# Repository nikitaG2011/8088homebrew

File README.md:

just run the make comand to assemble the code

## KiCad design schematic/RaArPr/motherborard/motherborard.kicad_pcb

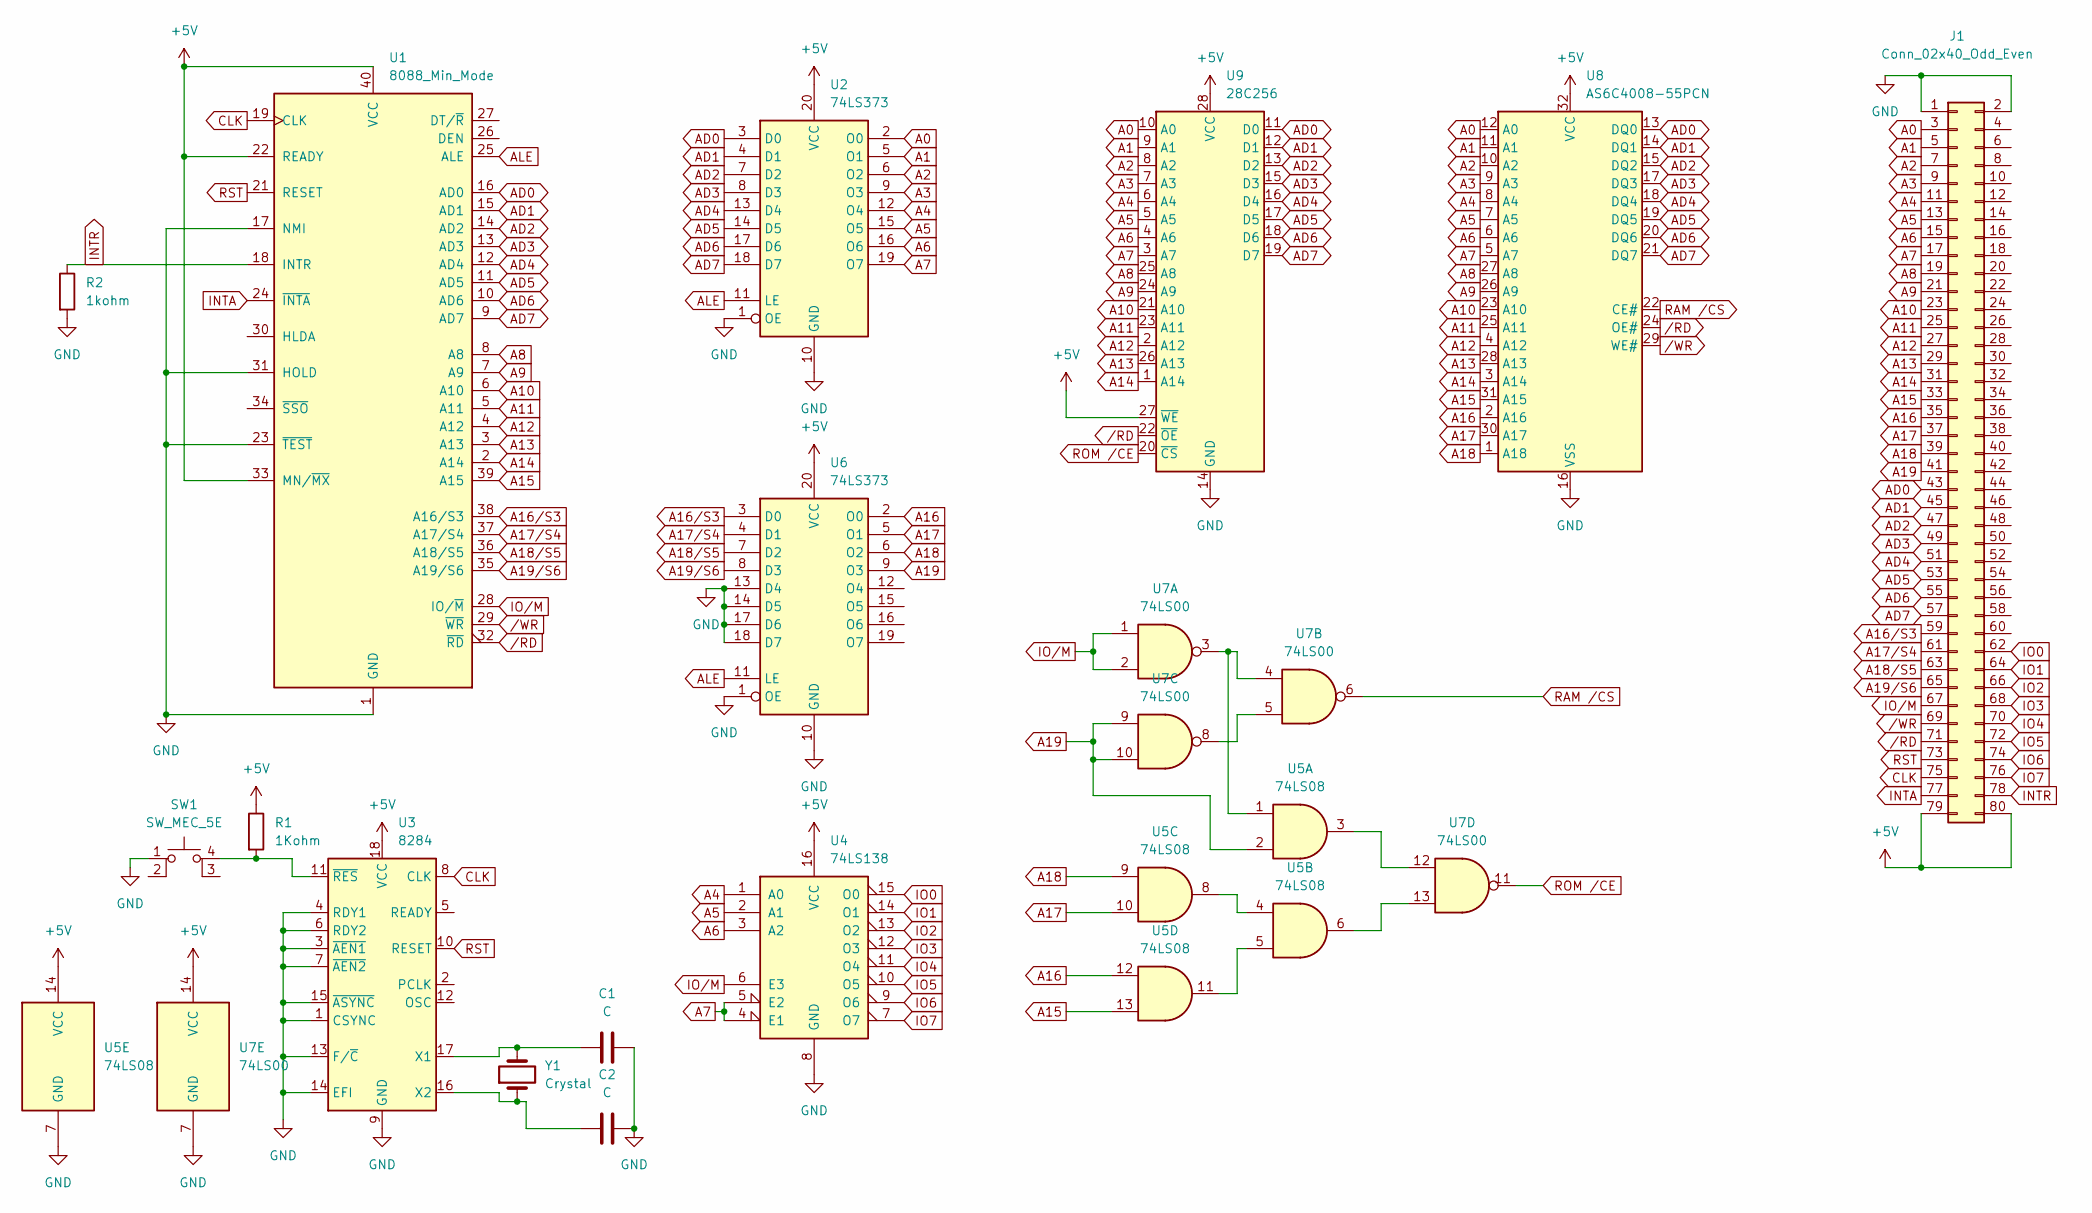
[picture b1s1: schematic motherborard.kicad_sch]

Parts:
C1, C2: C; C_Axial_L3.8mm_D2.6mm_P7.50mm_Horizontal
J1: Conn_02x40_Odd_Even; PinHeader_2x40_P2.54mm_Horizontal
R1: 1Kohm; R_Axial_DIN0204_L3.6mm_D1.6mm_P5.08mm_Horizontal
R2: 1kohm; R_Axial_DIN0204_L3.6mm_D1.6mm_P5.08mm_Horizontal
SW1: SW_MEC_5E; SW_MEC_5GSH9
U1: 8088_Min_Mode; DIP-40_W15.24mm
U2, U6: 74LS373; DIP-20_W7.62mm_Socket_LongPads
U3: 8284; DIP-18_W7.62mm_Socket_LongPads
U4: 74LS138; DIP-16_W7.62mm_Socket_LongPads
U5: 74LS08; DIP-14_W7.62mm_Socket_LongPads
U7: 74LS00; DIP-14_W7.62mm_Socket_LongPads
U8: AS6C4008-55PCN; DIP-32_W15.24mm_Socket_LongPads
U9: 28C256; DIP-28_W15.24mm_LongPads
Y1: Crystal; Crystal_HC18-U_Horizontal

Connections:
+5V: J1.79, J1.80, R1.1, U1.22 (READY), U1.33 (MN/~MX), U1.40 (VCC), U2.20 (VCC), U3.18 (VCC), U4.16 (VCC), U5.14 (VCC), U6.20 (VCC), U7.14 (VCC), U8.32 (VCC), U9.27 (~WE), U9.28 (VCC)
A0: J1.3, U2.2 (O0), U8.12 (A0), U9.10 (A0)
A1: J1.5, U2.5 (O1), U8.11 (A1), U9.9 (A1)
A2: J1.7, U2.6 (O2), U8.10 (A2), U9.8 (A2)
A3: J1.9, U2.9 (O3), U8.9 (A3), U9.7 (A3)
A4: J1.11, U2.12 (O4), U4.1 (A0), U8.8 (A4), U9.6 (A4)
A5: J1.13, U2.15 (O5), U4.2 (A1), U8.7 (A5), U9.5 (A5)
A6: J1.15, U2.16 (O6), U4.3 (A2), U8.6 (A6), U9.4 (A6)
A7: J1.17, U2.19 (O7), U4.4 (E1), U4.5 (E2), U8.5 (A7), U9.3 (A7)
A8: J1.19, U1.8 (A8), U8.27 (A8), U9.25 (A8)
A9: J1.21, U1.7 (A9), U8.26 (A9), U9.24 (A9)
A10: J1.23, U1.6 (A10), U8.23 (A10), U9.21 (A10)
A11: J1.25, U1.5 (A11), U8.25 (A11), U9.23 (A11)
A12: J1.27, U1.4 (A12), U8.4 (A12), U9.2 (A12)
A13: J1.29, U1.3 (A13), U8.28 (A13), U9.26 (A13)
A14: J1.31, U1.2 (A14), U8.3 (A14), U9.1 (A14)
A15: J1.33, U1.39 (A15), U5.13, U8.31 (A15)
A16: J1.35, U5.12, U6.2 (O0), U8.2 (A16)
A16/S3: J1.59, U1.38 (A16/S3), U6.3 (D0)
A17: J1.37, U5.10, U6.5 (O1), U8.30 (A17)
A17/S4: J1.61, U1.37 (A17/S4), U6.4 (D1)
A18: J1.39, U5.9, U6.6 (O2), U8.1 (A18)
A18/S5: J1.63, U1.36 (A18/S5), U6.7 (D2)
A19: J1.41, U5.2, U6.9 (O3), U7.9, U7.10
A19/S6: J1.65, U1.35 (A19/S6), U6.8 (D3)
AD0: J1.43, U1.16 (AD0), U2.3 (D0), U8.13 (DQ0), U9.11 (D0)
AD1: J1.45, U1.15 (AD1), U2.4 (D1), U8.14 (DQ1), U9.12 (D1)
AD2: J1.47, U1.14 (AD2), U2.7 (D2), U8.15 (DQ2), U9.13 (D2)
AD3: J1.49, U1.13 (AD3), U2.8 (D3), U8.17 (DQ3), U9.15 (D3)
AD4: J1.51, U1.12 (AD4), U2.13 (D4), U8.18 (DQ4), U9.16 (D4)
AD5: J1.53, U1.11 (AD5), U2.14 (D5), U8.19 (DQ5), U9.17 (D5)
AD6: J1.55, U1.10 (AD6), U2.17 (D6), U8.20 (DQ6), U9.18 (D6)
AD7: J1.57, U1.9 (AD7), U2.18 (D7), U8.21 (DQ7), U9.19 (D7)
ALE: U1.25 (ALE), U2.11 (LE), U6.11 (LE)
CLK: J1.75, U1.19 (CLK), U3.8 (CLK)
GND: C1.2, C2.2, J1.1, J1.2, R2.2, SW1.1, U1.1 (GND), U1.17 (NMI), U1.20 (GND), U1.23 (~TEST), U1.31 (HOLD), U2.1 (OE), U2.10 (GND), U3.1 (CSYNC), U3.3 (~AEN1), U3.4 (RDY1), U3.6 (RDY2), U3.7 (~AEN2), U3.9 (GND), U3.13 (F/~C), U3.14 (EFI), U3.15 (~ASYNC), U4.8 (GND), U5.7 (GND), U6.1 (OE), U6.10 (GND), U6.13 (D4), U6.14 (D5), U6.17 (D6), U6.18 (D7), U7.7 (GND), U8.16 (VSS), U9.14 (GND)
INTA: J1.77, U1.24 (~INTA)
INTR: J1.78, R2.1, U1.18 (INTR)
IO0: J1.62, U4.15 (O0)
IO1: J1.64, U4.14 (O1)
IO2: J1.66, U4.13 (O2)
IO3: J1.68, U4.12 (O3)
IO4: J1.70, U4.11 (O4)
IO5: J1.72, U4.10 (O5)
IO6: J1.74, U4.9 (O6)
IO7: J1.76, U4.7 (O7)
IO/M: J1.67, U1.28 (IO/~M), U4.6 (E3), U7.1, U7.2
unnamed: R1.2, SW1.4 (A), U3.11 (~RES)
unnamed: C1.1, U3.17 (X1), Y1.2
unnamed: C2.1, U3.16 (X2), Y1.1
unnamed: U5.1, U7.3, U7.4
unnamed: U5.3, U7.12
unnamed: U5.4, U5.8
unnamed: U5.6, U7.13
unnamed: U5.5, U5.11
unnamed: U7.5, U7.8
RAM /CS: U7.6, U8.22 (CE#)
ROM /CE: U7.11, U9.20 (~CS)
RST: J1.73, U1.21 (RESET), U3.10 (RESET)
/RD: J1.71, U1.32 (~RD), U8.24 (OE#), U9.22 (~OE)
/WR: J1.69, U1.29 (~WR), U8.29 (WE#)

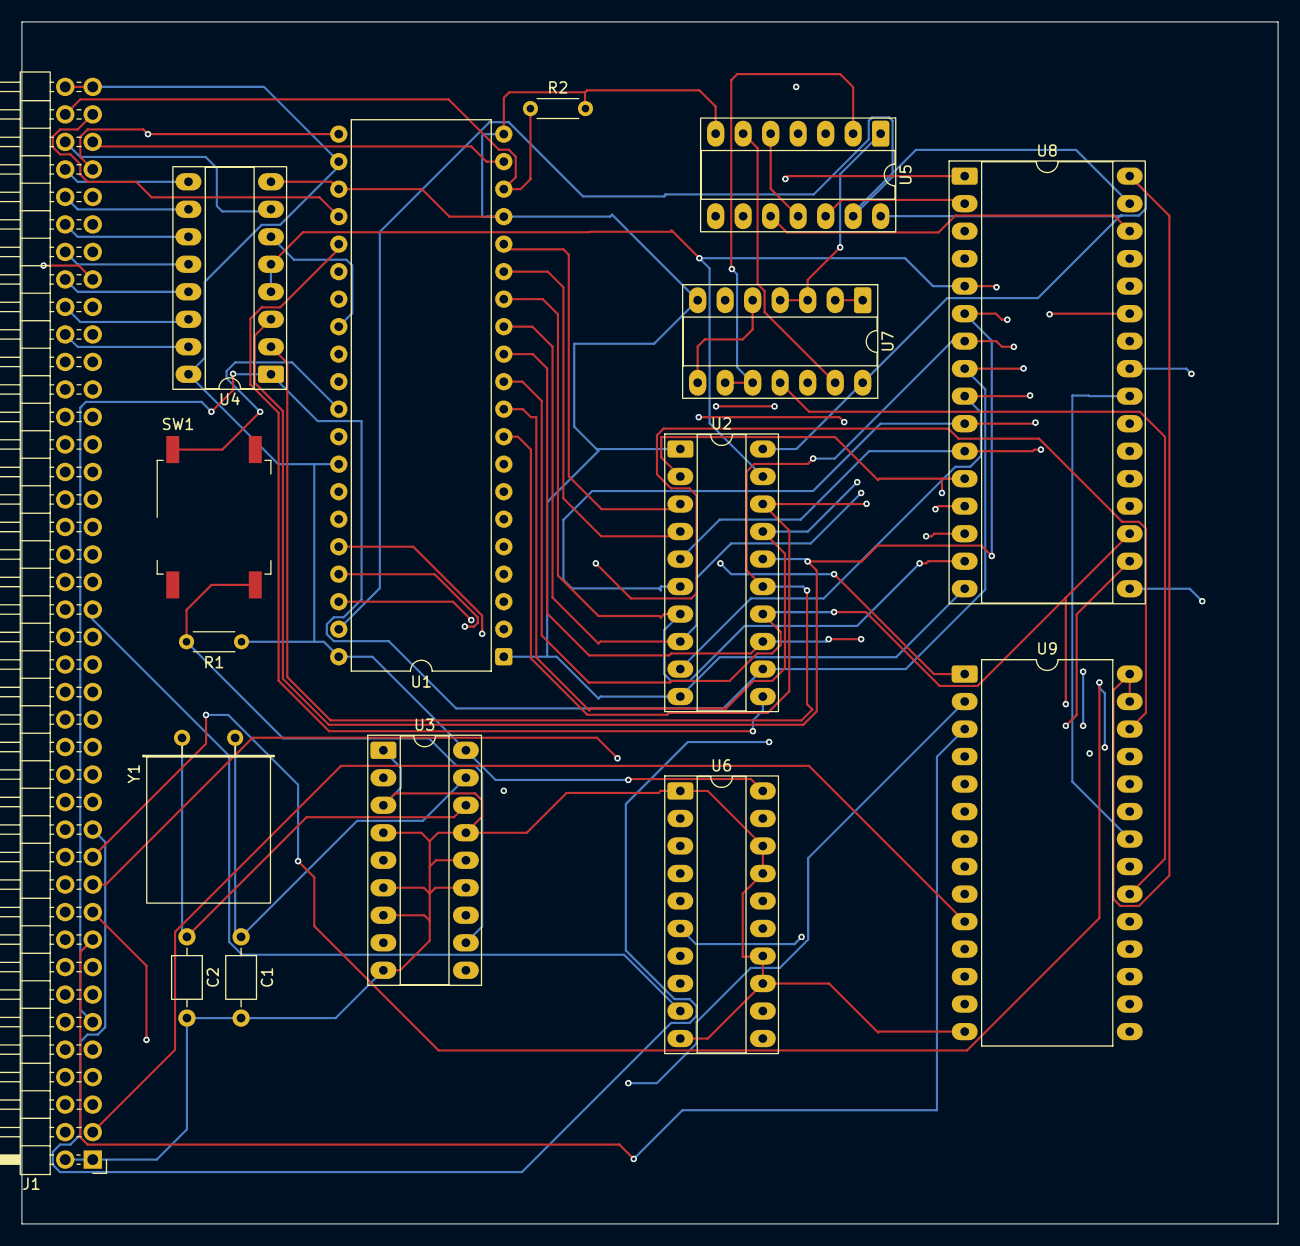
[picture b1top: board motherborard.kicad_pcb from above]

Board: 4 copper layers, 116.0 x 111.0 mm, 16 parts (0 on the bottom side), 61 nets.

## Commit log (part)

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2025-12-06 Add instructions to run make command
2025-12-11 just some names
2025-12-12 code
2025-12-13 code
    :D
2025-12-14 update to delay
2026-01-29 switched from nasm to jwasm
2026-01-30 swtched to nasm
2026-01-30 made windows build script
2026-01-30 finaly works!!!!!
2026-01-31 adding support for linux
2026-02-09 compile this your self
2026-02-11 arduino
2026-02-22 FIXY UPIE
2026-03-03 schematics
2026-03-27 new code
2026-03-27 more code
2026-03-31 ram works
2026-03-31 speed improvements'
2026-04-01 optimize
2026-04-04 hmmm hello there
2026-04-06 c code
2026-04-10 intr
2026-04-18 circ
2026-05-25 interupt
2026-05-27 ooooh code
